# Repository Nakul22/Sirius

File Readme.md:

Sirius - A Self-Localization System for Resource-Constrained IoT Sensors
====

Welcome to the Sirius Artifact repository. This repository contains artifacts and instructions for ACM Badging in Mobisys'23 proceedings.

The instructions for the artifacts provided are divided into the following sections:

1. [Hardware](#hardware) - Provides the necessary files and instructions to design, optimize and fabricate the reconfigurable antenna and the envelope detector. The antenna design and fabrication files are found in the [./hardware_schematics](./hardware_schematics) folder.

2. [Software](#software) - Provides the scripts, datasets and pretrained models to evaluate the angle-of-arrival estimation performance of the system. The matlab script [./aoa_performance/evaluate_aoa_estimation.m](./aoa_performance/evaluate_aoa_estimation.m) can be used to evaluate the performance of the AoA estimation. The matlab script [./localization_performance/evaluate_localization.m](./localization_performance/evaluate_localization.m) can be used to evaluate the localization performance based on the estimated AoA results.

# Hardware

## Hardware requirements

The hardware setup requires various components and tools during the design and fabrication process. Below is a list of components and tools we used for our prototype. However, users can choose to use any other available components.

| Component/Tool  | Link |
| ------------- | ------------- |
| FR4 PCB sheet  | https://www.amazon.com/dp/B07R592M7G/ref=cm_sw_em_r_mt_dp_64GBDSG48XJH234KXX3A?th=1  |
| PCB milling machine  | https://www.digikey.com/en/product-highlight/b/bantam-tools/desktop-pcb-milling-machine  |
| Pin diodes  | https://www.mouser.com/ProductDetail/Infineon-Technologies/BAR-50-02V-H6327?qs=mzcOS1kGbgfPFJ4O0G4Xhg%3D%3D  |
| Inductors  | https://www.mouser.com/ProductDetail/Coilcraft/C403-2/?qs=lc2O%252BfHJPVZCAfzA70W0Ag%3D%3D  |
| Capacitors  | https://www.digikey.com/en/products/detail/avx-corporation/ACCU-P0805KITL2/724571  |
| Schottky diodes | https://www.digikey.com/en/products/detail/skyworks-solutions-inc/SMS7630-079LF/2052135 |
| USRP N210 | https://www.ettus.com/all-products/un210-kit/ |
| Tx Power Amplifier | https://www.qorvo.com/products/p/RF5110G |

## Antenna Design 

The Sirius antenna prototypes have been designed to operate in the 900MHz and 2.4GHz ISM bands. We provide the Ansys HFSS design files for these antennas, which can be used along with the Eagle schematic files for PCB fabrication. The HFSS design files are located in [./HFSS_design](./HFSS_design). The .aedt file consists of the antenna model as well as the lumped components of the pin-diode based switches. These files can be opened with Ansys HFSS 2022R2 and can be modified for any desired frequency based on user requirements.

To help visualize the designed antenna's gain-patterns and S11 return loss (reflection coefficient), we have also included a MATLAB script called [./HFSS_design/show_antenna_gain_pattern.m](./HFSS_design/show_antenna_gain_pattern.m).

## Antenna Fabrication

We have provided BRD files for pre-tuned 900MHz and 2.4GHz antennas to allow users to directly fabricate the hardware. These files can be found in the [./hardware_schematics/reconfigurable_antennas](./hardware_schematics/reconfigurable_antennas) folder. For our prototypes, we used 1.5mm thick FR4 substrate and the Bantam PCB milling machine to fabricate double-sided PCBs. The antenna consists of two pin-diode switches along with DC blocking circuits, and the BRD file has solder pad placeholders for these components. While we used BAR50-02v pin-diodes in our prototype, any RF grade pin-diode should also work. We also utilized inductors as RF chokes to block AC current and isolate other wires from the antenna, resulting in improved performance. Additional details about antenna fabrication can be found in the accompanying paper.

## Envelope Detector

An envelope detector is used to extract the envelope of the received signal. We implemented a simple envelope detector circuit, which includes schottky diodes as rectifiers, a low pass filter, and an impedance matching network. The diode rectifies the signal, and the low pass filter eliminates high-frequency components. The schematic and BRD files for the envelope detector are available in the [./hardware_schematics/envelope_detector/](./hardware_schematics/envelope_detector/)" folder. Reference values for the low pass filter can be found in the paper.

Although not required, an impedance matching network can improve the sensitivity and range of the receiver. This network is used to match the impedance of the envelope detector to the impedance of the designed antenna (50ohms). The schematic and BRD files contain solder pads for capacitors and inductors in a pi-network. Users can choose to use the provided schematic or modify it based on their implementation. We suggest using a Vector Network Analyzer (VNA) to measure the impedance of both the antenna and the envelope detector for precise matching.

# Software

## Software requirements

Sirius implementation used the folllwing software tools for antenna design, PCB fabrication, and data processing. The table below lists the software used for each process.

| Process | Software used |
| ------------- | ------------- |
| Antenna Design  | Ansys HFSS  |
| PCB Fabrication  | Autodesk Eagle  |
| Data processing  | Matlab  |

We have validated the results on a Macbook Air M1 running Matlab 2023a. However, the provided scripts should work on any Linux or Windows machine with the following add-on packages installed.

| Matlab add-on package  | Version |
| ------------- | ------------- |
|DSP System Toolbox | 9.16 |
|Signal Processing Toolbox | 9.2 |
|Statistics and Machine Learning Toolbox | 12.5 |
|Communications Toolbox | 8.0 |
|Antenna Toolbox | 5.4 |
|Deep Learning Toolbox | 14.6 |
|Phased Array System Toolbox | 5.0 |

## Angle-of-arrival Performance

To evaluate the performance of the angle-of-arrival (AoA) estimation, we provide sample datasets and Matlab scripts in the [./aoa_performance](./aoa_performance) folder. These datasets include real world experiments data collected for the 900Mhz reconfigurable antenna. The test data and pretrained model are stored as .mat files. Running the "evaluate_aoa_estimation.m" script will load the test data and pretrained model, and evaluate the AoA estimation performance. The script also generates plots of the CDF of angle-errors and a scatter plot of the estimated angles. These plots reflect the core results of the paper and demonstrate the overall system performance, as shown in section "AoA Performance" of the paper.

## Localization Performance

To evaluate the performance of localization, we provide sample AoA outputs of all the outdoor expeirmentand corresponding Matlab scripts in the [./localization_performance](./localization_performance) folder. These datasets include real world experiments data collected for the 900Mhz reconfigurable antenna. The aoa results were obtained using the above mentined aoa scripts. Running the "evaluate_localization.m" script will load the aoa data and perform triangualtion to obtain the locations for each experiment iteration. The script also generates plots of the CDF of localization-errors. These plots reflect the localization results of the paper and demonstrate the overall system performance, as shown in evaluation section "Localization" of the paper.

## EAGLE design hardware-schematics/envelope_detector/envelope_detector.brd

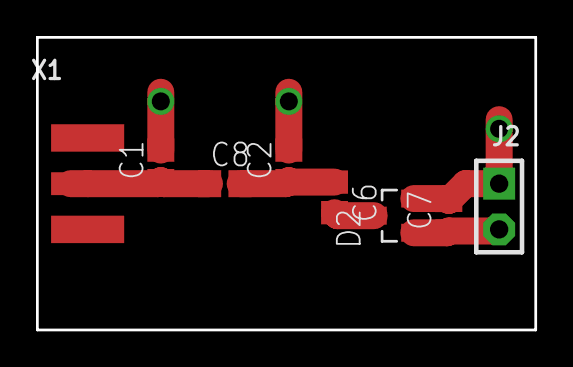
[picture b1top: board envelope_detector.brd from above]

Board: 2 copper layers, 27.7 x 16.3 mm, 8 parts (0 on the bottom side), 5 nets.

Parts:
C1, C2, C6, C7, C8: C0805
D2: BAS40-04; SOT23
J2: F-1X02-SIP-100-40; SIP-100-02-40
X1: SMA_EDGELAUNCH

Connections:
GND: C1.2, C2.2, C7.2, D2.2, J2.1, X1.GND@1, X1.GND@2, X1.GND@3, X1.GND@4
unnamed: C7.1, D2.1, J2.2
unnamed: C6.2, D2.3
unnamed: C1.1, C8.1, X1.P
unnamed: C2.1, C6.1, C8.2

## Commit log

2023-04-10 Articat repository created
2023-04-11 Updated readme file
2023-04-11 Artifact repository updated

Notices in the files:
parts and their libraries:
con-headers-jp: Copyright (C) 2008, Bob Starr
